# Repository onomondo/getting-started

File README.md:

# Onomondo getting started kit. 

Example forked from [esp-idf repo](https://github.com/espressif/esp-idf/tree/master/examples/protocols/pppos_client). 

## What is this?
The kit is designed to showcase some of the features provided by Onomondo. Already a customer? Head over to [app.onomondo.com/getting-started](https://app.onomondo.com/getting-started) to get a guided tour of the platform and to see the data packets in real-time. 

### Onomondo Connectors 
Specifically, this example is powered by the Onomondo Connectors. It removes complexity (i.e. Cloud SDK) from the device and let the network handle it. Check out the code snippet below - would you have guessed that this is fully encrypted and integrated into the *Azure IoT Hub*? Get more info on Connectors [here](https://help.onomondo.com/what-are-onomondo-connectors). 

```c
//init cellular connectivity
esp_err_t status = initCellular(SIM7xxx, 0);
...
...
// setup of sensor
...
...
// open a socket to a non-existing server
status = openSocket("1.2.3.4", 4321);

// payload formatting
sprintf(payload, "{\"battery\": %f,\"signal\": %f,\"temperature\": %f}", battery, signal, temp);

// transmit payload
status = sendData(payload, strlen(payload), 0);
```

This it what happens on the platform: 
<!--  -->

At this point the data has not yet reached any public networks. Since the SIM has a Connector configured, the payload gets neatly wrapped up and securely handed over to *Azure IoT Hub* (but not limited to *Azure*: Want a webhook event: ✔, any major cloud provider ✔, custom TLS endpoint ✔).    

This is from the *Azure Logs*:

Notice how the network has added a few fields: A timestamp and a sim_id so the device can be identified. In addition to the extra fields everything has been fully encrypted. 

## How to use. 

The kit is fully programmed when you get it. However, you are encouraged to modify the example we have provided. 

First time use: Flick the power switch and the device should come online. The device will search for networks, register on a network and establish a data connection. Touch the touch-pad on the front to transmit a message with the current temperature, battery voltage and last known signal level. After a while the device will enter a low power state. Give it a shake to wake it up again. 

### Get the demo tour
On [app.onomondo.com/getting-started](https://app.onomondo.com/getting-started) you'll get the full tour. 

### Flash a precompiled firmware
In case the stock firmware gets overwritten, you can easily flash the device with a precompiled binary. Download the *ESP flash download tool* [here](https://www.espressif.com/en/support/download/other-tools?keys=download+tool), download the precompiled firmware (**onomondo_getting_started.bin**) from the repo and flash the device. 

These procompiled binaries will in the future include firmware to assist in debugging connectivity with Onomondo. 

### Build and Flash Modified firmware. 

Run `idf.py --ccache -p PORT build flash monitor` to build and flash the project..

(To exit the serial monitor, type ``Ctrl-]``.)

See the [ESP-IDF Getting Started Guide](https://docs.espressif.com/projects/esp-idf/en/latest/get-started/index.html) for full steps to configure and use ESP-IDF to build projects. 

## Troubleshooting
If the device fails to connect (red flashing LED).  
1. Is the sim activated
2. Attaching for the first time can be slow in some cases. 
3. Is the antenna plugged in?
4. Is there sufficient charge on the battery? If the battery is discharged the device won't turn on until it has been plugged into a charger. 

Check the Network logs on the Onomondo platform. Does the platform report any activity?

Plug the device into you computer (use the port marked as MCU Debug on the back). Have a look at the out below and see if anything stands out. Does the modem reponds to any commands? When does it stop responding? 

## Example Output

### SIM7070G Output
```bash
I (451) main: Cpu freq: 160 MhZ
I (451) ACC: Config i2c param
I (461) ACC: Install i2c driver
I (461) ACC: Reading register....
I (481) main: Temperature: 26.500000
I (481) gpio: GPIO[4]| InputEn: 0| OutputEn: 1| OpenDrain: 0| Pullup: 0| Pulldown: 0| Intr:0
I (481) gpio: GPIO[5]| InputEn: 0| OutputEn: 1| OpenDrain: 0| Pullup: 0| Pulldown: 0| Intr:0
I (491) gpio: GPIO[25]| InputEn: 0| OutputEn: 1| OpenDrain: 0| Pullup: 0| Pulldown: 0| Intr:0
I (511) touch_driver: test init: touch pad [6] val is 686
I (511) uart: queue free spaces: 30
I (511) sim800: PWR pin 27
I (511) gpio: GPIO[27]| InputEn: 0| OutputEn: 1| OpenDrain: 0| Pullup: 0| Pulldown: 0| Intr:0
I (521) AT CMD: AT
E (621) esp-modem: esp_modem_dte_send_cmd(352): process command timeout
E (621) dce_service: esp_modem_dce_power_test(251): send command failed
I (721) AT CMD: AT
I (721) AT RESP: AT

E (721) esp-modem: esp_dte_handle_line(136): handle line failed
E (721) esp-modem: AT

I (721) AT RESP: OK

I (721) sim800: Modem is on!
I (731) AT CMD: AT
I (731) AT RESP: AT

E (731) esp-modem: esp_dte_handle_line(136): handle line failed
E (741) esp-modem: AT

I (741) AT RESP: OK

I (751) AT CMD: ATE0
I (751) AT RESP: ATE0

E (751) esp-modem: esp_dte_handle_line(136): handle line failed
E (761) esp-modem: ATE0

I (761) AT RESP: OK

I (761) AT CMD: AT+CGMM
I (771) AT RESP:

I (771) AT RESP: SIMCOM_SIM7070

I (781) AT RESP:

I (781) AT RESP: OK

I (781) AT CMD: AT+CGSN
I (791) AT RESP:

I (791) AT RESP: 861340049970997

I (791) AT RESP:

I (791) AT RESP: OK

I (801) AT CMD: AT+COPS?
I (801) AT RESP:

I (801) AT RESP: +COPS: 1,0,"TDC",7

I (811) AT RESP:

I (811) AT RESP: OK

I (811) AT CMD: AT+CREG?
I (821) AT RESP:

I (821) AT RESP: +CREG: 0,5

I (821) AT RESP:

I (831) AT RESP: OK

I (831) AT CMD: AT+CBANDCFG="CAT-M",3,8,20
I (841) AT RESP:

I (841) AT RESP: OK

I (841) AT CMD: AT+CNMP=38
I (851) AT RESP:

I (851) AT RESP: OK

I (851) esp-modem: No handler for line: OK

E (851) esp-modem: OK

E (1341) esp-modem: esp_modem_dte_send_cmd(352): process command timeout
I (1341) sim800: Modem INIT OK, 0x3ffbf604
I (1341) AT CMD: AT+IFC=0,0
I (1341) AT RESP:

I (1341) AT RESP: OK

I (1351) AT CMD: AT+CREG?
I (1351) AT RESP:

I (1351) AT RESP: +CREG: 0,5

I (1361) AT RESP:

I (1361) AT RESP: OK

I (1361) cellular: Module: SIMCOM_SIM7070
I (1371) cellular: Operator: "TDC"
I (1371) cellular: IMEI: 861340049970997
I (1381) cellular: IMSI:
I (1381) AT CMD: AT+CSQ
I (1381) AT RESP:

I (1391) AT RESP: +CSQ: 31,99

I (1391) AT RESP:

I (1391) AT RESP: OK

I (1401) cellular: rssi: 31, ber: 99
I (1401) AT CMD: AT+CEDRXS=1,4,"0010"
I (1411) AT RESP:

I (1411) AT RESP: OK

I (1411) AT CMD: AT+CEDRXRDP
I (1421) AT RESP:

I (1421) AT RESP: +CEDRXRDP: 4,"0010","0010","0000"

I (1421) eDRX CHECK: Supported
I (1431) AT RESP:

I (1431) AT RESP: OK

I (1431) AT CMD: AT+CPSMRDP
I (1441) AT RESP:

I (1441) AT RESP: +CPSMRDP: 0,20,14400,0,0,3600

I (1441) PSM CHECK: +CPSMRDP: 0,20,14400,0,0,3600

I (1451) PSM CHECK: 0,20,14400,0,0,3600
I (1451) PSM CHECK: Active: 0
I (1461) AT RESP:

I (1461) AT RESP: OK

I (1461) AT CMD: AT+CPSI?
I (1471) AT RESP:

I (1481) AT RESP: +CPSI: LTE CAT-M1,Online,238-01,0x07D0,12024586,465,EUTRAN-BAND20,6350,5,5,-16,-83,-53,10

E (1481) esp-modem: esp_dte_handle_line(136): handle line failed
E (1491) esp-modem: +CPSI: LTE CAT-M1,Online,238-01,0x07D0,12024586,465,EUTRAN-BAND20,6350,5,5,-16,-83,-53,10

I (1501) AT RESP:

I (1501) AT RESP: OK

I (1501) AT CMD: AT+CPSMRDP
I (1511) AT RESP:

I (1511) AT RESP: +CPSMRDP: 0,20,14400,0,0,3600

I (1521) PSM CHECK: +CPSMRDP: 0,20,14400,0,0,3600

I (1521) PSM CHECK: 0,20,14400,0,0,3600
I (1531) PSM CHECK: Active: 0
I (1531) AT RESP:

I (1531) AT RESP: OK

I (1541) AT CMD: AT+CGDCONT=1,"IP","onomondo"
I (1551) AT RESP:

I (1551) AT RESP: OK

I (1551) dce_service: define pdp context ok
I (1551) sim800: Working mode is changed! :D
I (1561) AT CMD: ATD*99#
I (1561) AT RESP:

I (1561) AT RESP: CONNECT 150000000

I (1671) cellular: Modem PPP Started
I (1671) cellular: PPP state changed event 259
I (1671) cellular: PPP state changed event 262
I (1691) cellular: PPP state changed event 263
I (1691) cellular: PPP state changed event 265
I (1711) esp-netif_lwip-ppp: Connected
I (1711) esp-netif_lwip-ppp: Name Server1: 10.85.59.251
I (1711) esp-netif_lwip-ppp: Name Server2: 10.85.59.242
I (1721) cellular: Modem Connect to PPP Server
I (1721) cellular: ~~~~~~~~~~~~~~
I (1731) cellular: IP          : 100.68.57.55
I (1731) cellular: Netmask     : 255.255.255.255
I (1741) cellular: Gateway     : 10.64.64.64
I (1741) cellular: Name Server1: 10.85.59.251
I (1751) cellular: Name Server2: 10.85.59.242
I (1751) cellular: ~~~~~~~~~~~~~~
I (1761) cellular: GOT ip event!!!
I (1761) cellular: PPP state changed event 266
I (1771) cellular: Socket created, connecting to 1.2.3.4:4321
I (3161) Transmit: {"battery": 0.284000,"signal": 31.000000,"temperature": 26.625000}
W (20361) ACC: Wakeup interrupt NOT active...,00000000
```

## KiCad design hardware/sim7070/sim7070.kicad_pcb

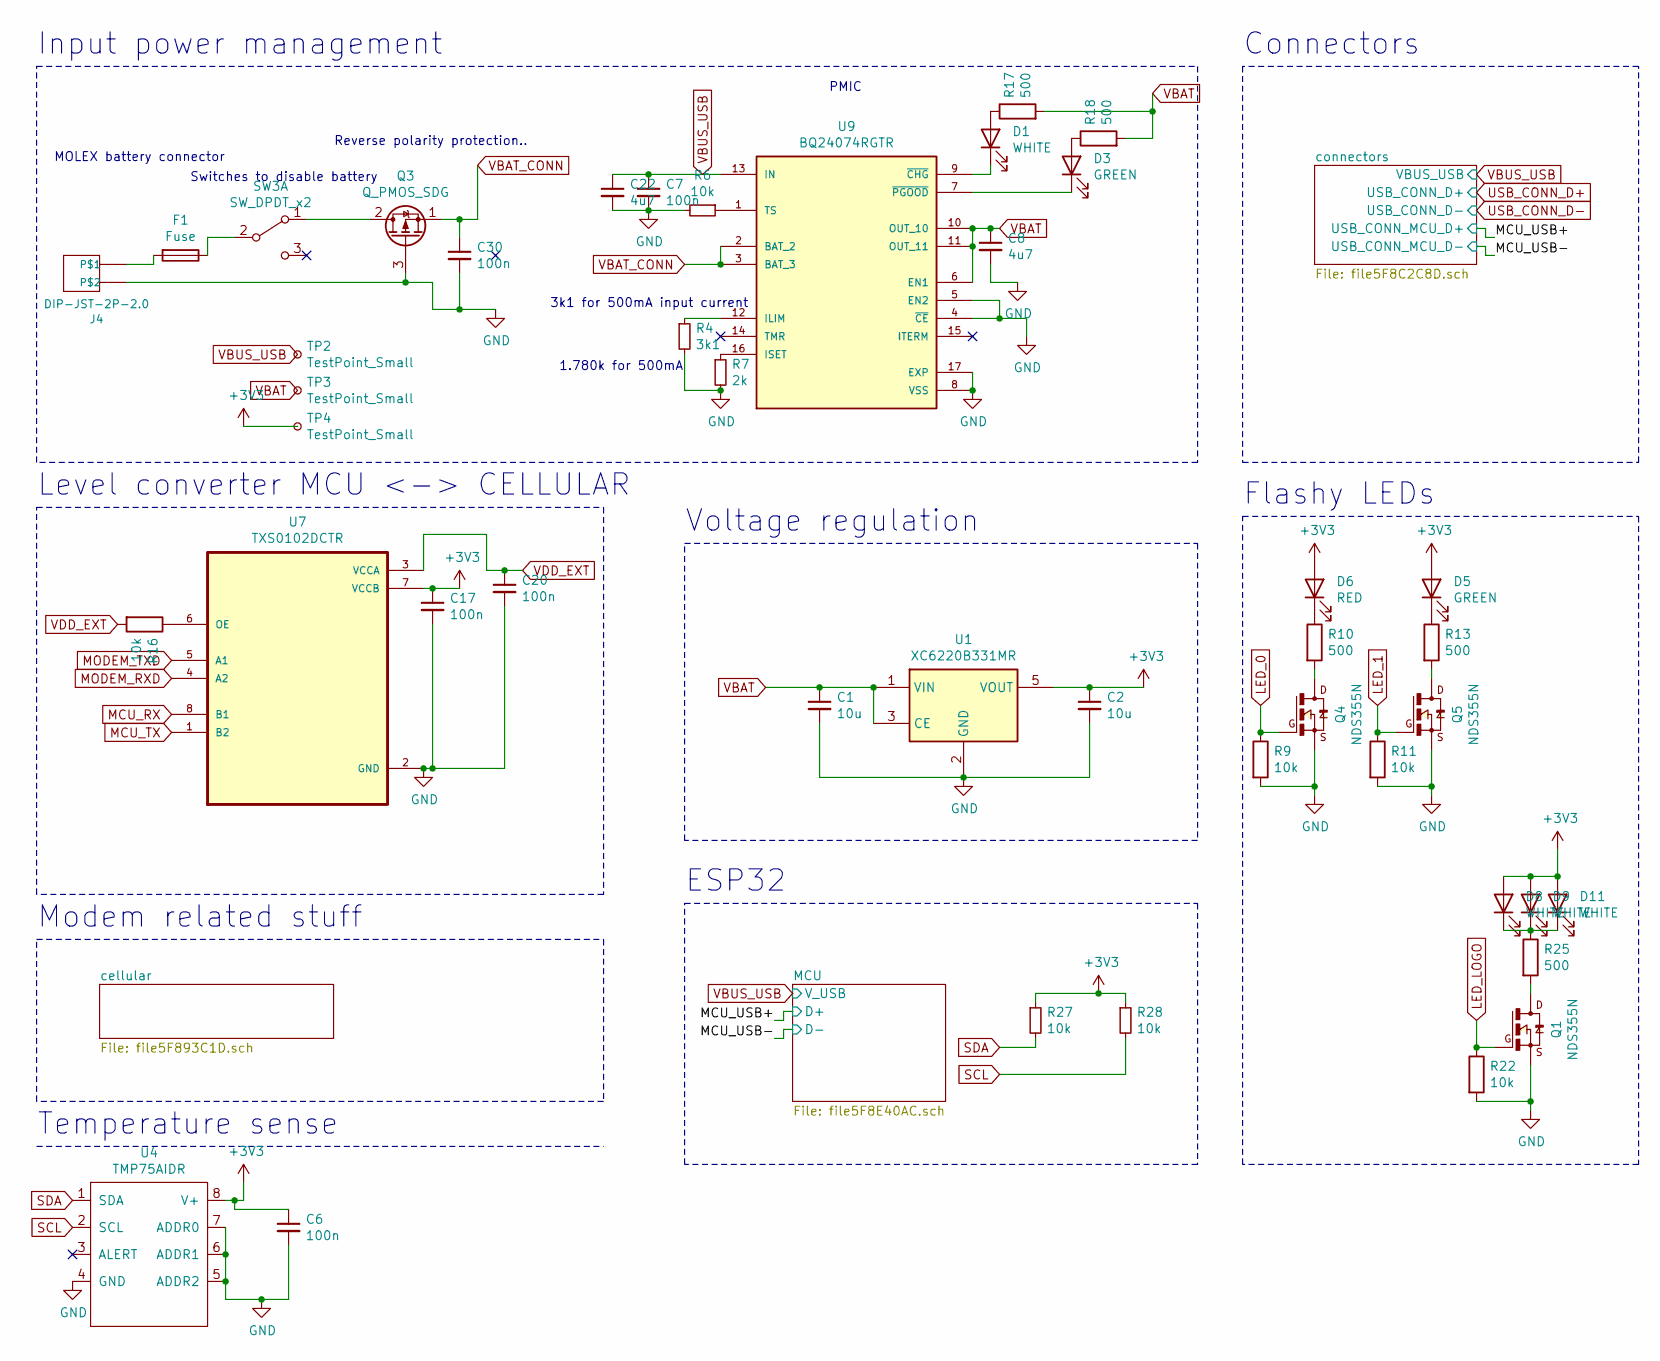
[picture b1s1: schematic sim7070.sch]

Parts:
C1, C2: 10u; C_0603_1608Metric; LCSC C19702
C6, C7, C17, C20, C30: 100n; C_0402_1005Metric; LCSC C1525
C8: 4u7; C_1206_3216Metric; LCSC C29823
C22: 4u7; C_1206_3216Metric
D1, D8, D9, D11: WHITE; LED_0603_1608Metric; LCSC C2290
D3: GREEN; LED_0603_1608Metric
D5: GREEN; LED_0603_1608Metric; LCSC C2286
D6: RED; LED_0603_1608Metric; LCSC C2286
F1: Fuse; Fuse_0603_1608Metric; LCSC C163117
J4: DIP-JST-2P-2.0; JST_PH_S2B-PH-K_1x02_P2.00mm_Horizontal; LCSC C173752
Q1, Q4, Q5: NDS355N; SSOT-3; LCSC C113202
Q3: Q_PMOS_SDG; SOT-23-MOSFET; LCSC C10487
R4: 3k1; R_0402_1005Metric; LCSC C26077
R6, R9, R11, R22, R27, R28: 10k; R_0402_1005Metric; LCSC C25531
R7: 2k; R_0402_1005Metric; LCSC C25552
R10, R13, R17, R18, R25: 500; R_0603_1608Metric; LCSC C23179
R16: 10k; R_0402_1005Metric
SW3: SW_DPDT_x2; SWITCH_3A; LCSC C319015
TP2, TP3, TP4: TestPoint_Small; TestPoint_Pad_1.5x1.5mm
U1: XC6220B331MR; SOT-23-5; LCSC C86534
U4: TMP75AIDR; SOIC-8_3.9x4.9mm_P1.27mm; LCSC C30389
U7: TXS0102DCTR; SOP65P400X130-8N; LCSC C324082
U9: BQ24074RGTR; QFN50P300X300X100-17N; PARTREV M; LCSC C54313

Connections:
+3V3: C2.1, C6.1, C17.1, D5.2 (A), D6.2 (A), D8.2 (A), D9.2 (A), D11.2 (A), R27.1, R28.1, TP4.1, U1.5 (VOUT), U4.8 (V+), U7.7 (VCCB); also elsewhere on the board
GND: C1.2, C2.2, C6.2, C7.2, C8.2, C17.2, C20.2, C22.2, C30.2, J4.2, Q1.2, Q3.3 (G), Q4.2, Q5.2, R4.2, R6.2, R7.2, R9.2, R11.2, R22.2, U1.2 (GND), U4.4 (GND), U4.5 (ADDR2), U4.6 (ADDR1), U4.7 (ADDR0), U7.2 (GND), U9.4 (~CE), U9.5 (EN2), U9.8 (VSS), U9.17 (EXP), U9.18, U9.19, U9.20, U9.21, U9.22; also elsewhere on the board
LED_0: Q4.1, R9.1; also elsewhere on the board
LED_1: Q5.1, R11.1; also elsewhere on the board
LED_LOGO: Q1.1, R22.1; also elsewhere on the board
MCU_RX: U7.8 (B1); also elsewhere on the board
MCU_TX: U7.1 (B2); also elsewhere on the board
MODEM_RXD: U7.4 (A2); also elsewhere on the board
MODEM_TXD: U7.5 (A1); also elsewhere on the board
unnamed: D1.1 (K), U9.9 (~CHG)
unnamed: D1.2 (A), R17.1
unnamed: D3.1 (K), U9.7 (~PGOOD)
unnamed: D3.2 (A), R18.1
unnamed: D5.1 (K), R13.1
unnamed: D6.1 (K), R10.1
unnamed: D8.1 (K), D9.1 (K), D11.1 (K), R25.1
unnamed: F1.1, SW3.2 (B)
unnamed: F1.2, J4.1
unnamed: Q1.3, R25.2
unnamed: Q3.2 (D), SW3.1 (A)
unnamed: Q4.3, R10.2
unnamed: Q5.3, R13.2
unnamed: R4.1, U9.12 (ILIM)
unnamed: R6.1, U9.1 (TS)
unnamed: R7.1, U9.16 (ISET)
unnamed: R16.1, U7.6 (OE)
SCL: R28.2, U4.2 (SCL); also elsewhere on the board
SDA: R27.2, U4.1 (SDA); also elsewhere on the board
VBAT: C1.1, C8.1, R17.2, R18.2, TP3.1, U1.1 (VIN), U1.3 (CE), U9.6 (EN1), U9.10 (OUT_10), U9.11 (OUT_11); also elsewhere on the board
VBAT_CONN: C30.1, Q3.1 (S), U9.2 (BAT_2), U9.3 (BAT_3); also elsewhere on the board
VBUS_USB: C7.1, C22.1, TP2.1, U9.13 (IN); also elsewhere on the board
VDD_EXT: C20.1, R16.2, U7.3 (VCCA); also elsewhere on the board

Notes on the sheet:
Reverse polarity protection..
Switches to disable battery
MOLEX battery connector
1.780k for 500mA
3k1 for 500mA input current
PMIC
Input power management
Level converter MCU <-> CELLULAR
Voltage regulation
Modem related stuff
ESP32
Connectors
Flashy LEDs
Temperature sense

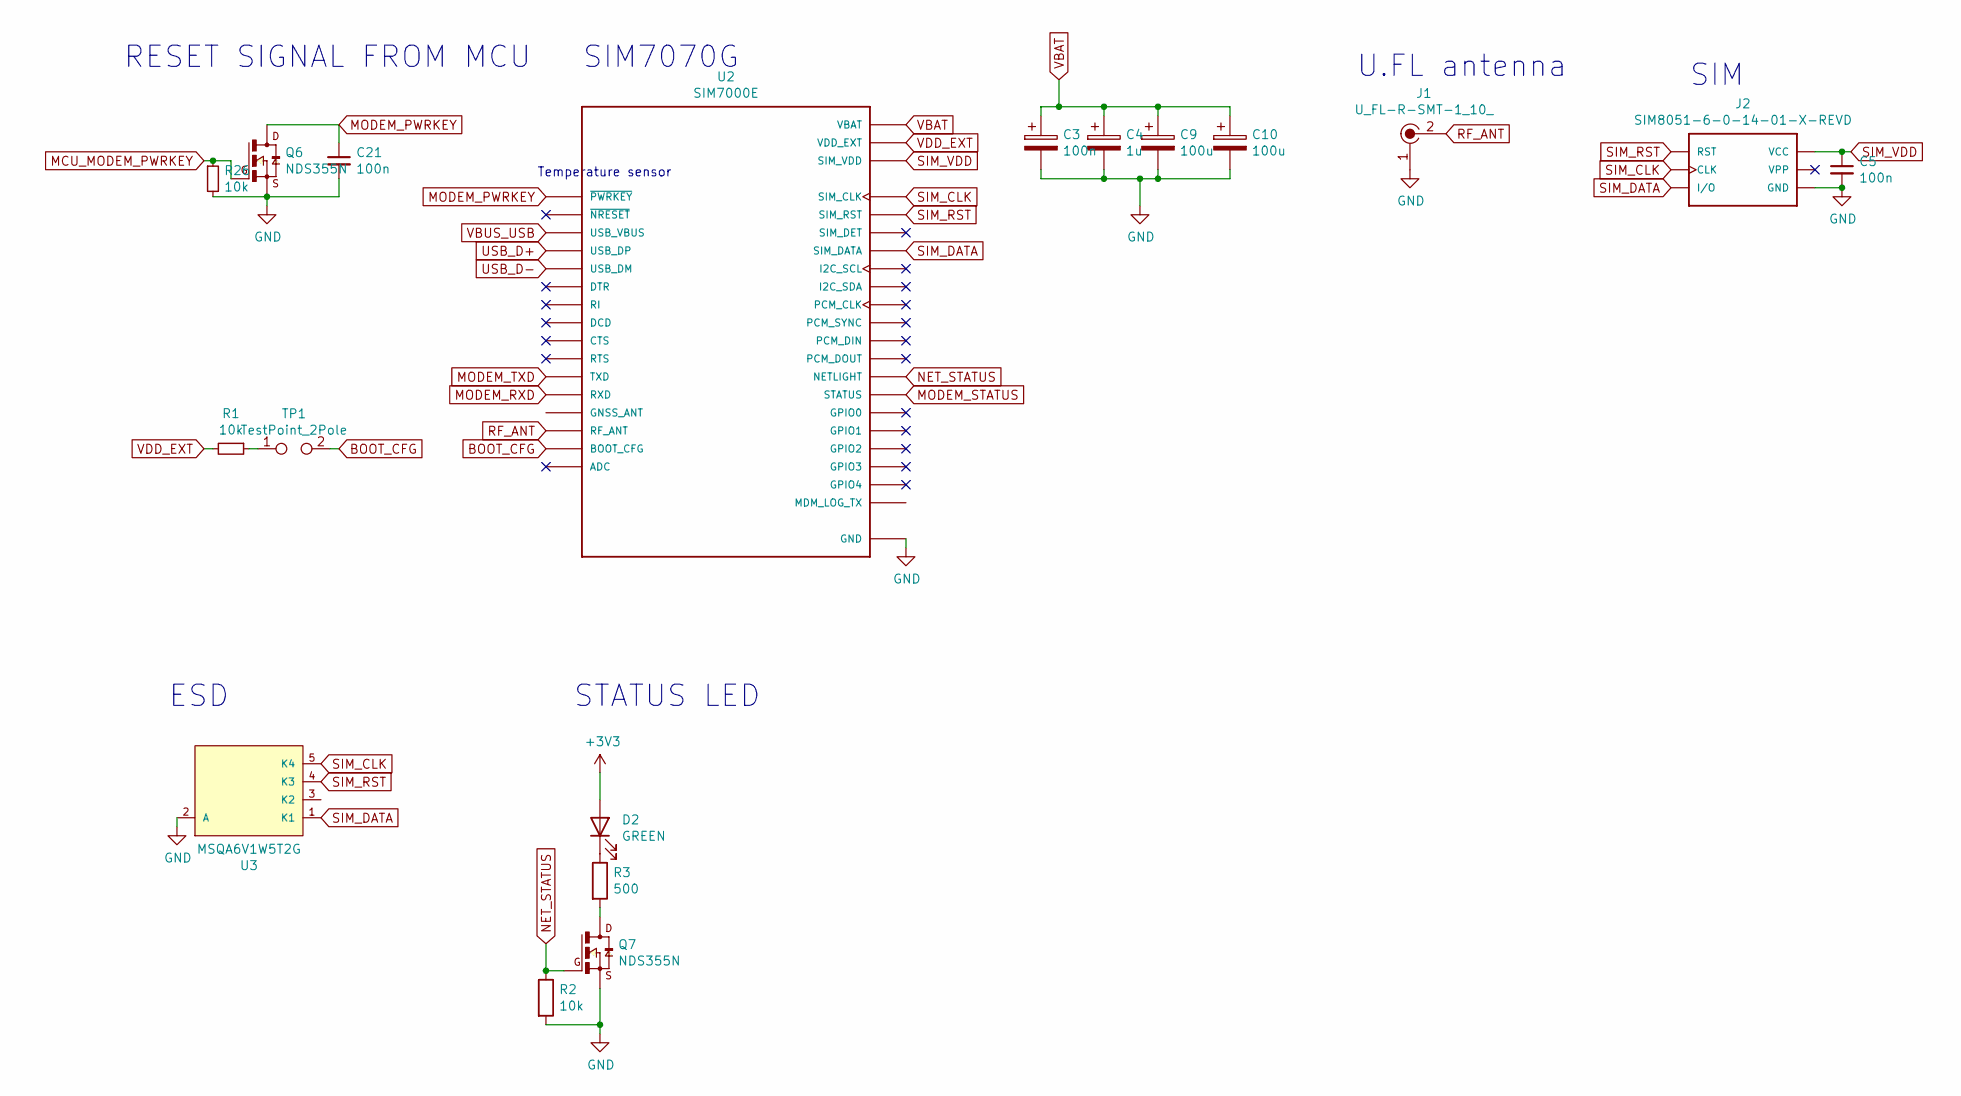
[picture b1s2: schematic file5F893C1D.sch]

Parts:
C3, C5, C21: 100n; C_0402_1005Metric; LCSC C1525
C4: 1u; C_0805_2012Metric; LCSC C28323
C9: 100u; C_1206_3216Metric; LCSC C15008
C10: 100u; C_1206_3216Metric
D2: GREEN; LED_0603_1608Metric
J1: U_FL-R-SMT-1_10_; Coax_Conn_U.FL; MPN U.FL-R-SMT-1(10); Digi-Key_PN H11891CT-ND
J2: SIM8051-6-0-14-01-X-REVD; SNO-1305-B_NANO_SIM; LCSC C111371
Q6, Q7: NDS355N; SSOT-3; LCSC C113202
R1: 10k; R_0402_1005Metric
R2, R26: 10k; R_0402_1005Metric; LCSC C25531
R3: 500; R_0603_1608Metric; LCSC C23179
TP1: TestPoint_2Pole; SolderJumper-2_P1.3mm_Open_Pad1.0x1.5mm
U2: SIM7000E; SIMCON_SIM7000E
U3: MSQA6V1W5T2G; On_Semiconductor-MSQA6V1W5T2G-Manufacturer_Recommended; LCSC C232563

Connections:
+3V3: D2.2 (A); also elsewhere on the board
BOOT_CFG: TP1.2, U2.6 (BOOT_CFG)
GND: C3.2, C4.2, C5.2, C9.2, C10.2, C21.2, J1.1, J2.C5 (GND), Q6.2, Q7.2, R2.2, R26.2, U2.2 (GND), U2.17 (GND), U2.18 (GND), U2.29 (GND), U2.39 (GND), U2.45 (GND), U2.46 (GND), U2.54 (GND), U2.58 (GND), U2.59 (GND), U2.61 (GND), U2.62 (GND), U2.63 (GND), U2.64 (GND), U2.65 (GND), U3.2 (A); also elsewhere on the board
MCU_MODEM_PWRKEY: Q6.1, R26.1; also elsewhere on the board
MODEM_PWRKEY: C21.1, Q6.3, U2.1 (~PWRKEY~); also elsewhere on the board
MODEM_RXD: U2.10 (RXD); also elsewhere on the board
MODEM_STATUS: U2.66 (STATUS)
MODEM_TXD: U2.9 (TXD); also elsewhere on the board
NET_STATUS: Q7.1, R2.1, U2.52 (NETLIGHT)
unnamed: D2.1 (K), R3.1
unnamed: Q7.3, R3.2
unnamed: R1.1, TP1.1
RF_ANT: J1.2, U2.60 (RF_ANT)
SIM_CLK: J2.C3 (CLK), U2.32 (SIM_CLK), U3.5 (K4)
SIM_DATA: J2.C7 (I/O), U2.31 (SIM_DATA), U3.1 (K1)
SIM_RST: J2.C2 (RST), U2.33 (SIM_RST), U3.4 (K3)
SIM_VDD: C5.1, J2.C1 (VCC), U2.30 (SIM_VDD)
USB_CONN_D+: U2.27 (USB_DP); also elsewhere on the board
USB_CONN_D-: U2.28 (USB_DM); also elsewhere on the board
VBAT: C3.1, C4.1, C9.1, C10.1, U2.55 (VBAT), U2.56 (VBAT), U2.57 (VBAT); also elsewhere on the board
VBUS_USB: U2.24 (USB_VBUS); also elsewhere on the board
VDD_EXT: R1.2, U2.15 (VDD_EXT); also elsewhere on the board

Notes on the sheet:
Temperature sensor
SIM7070G
U.FL antenna
SIM
RESET SIGNAL FROM MCU
ESD
STATUS LED

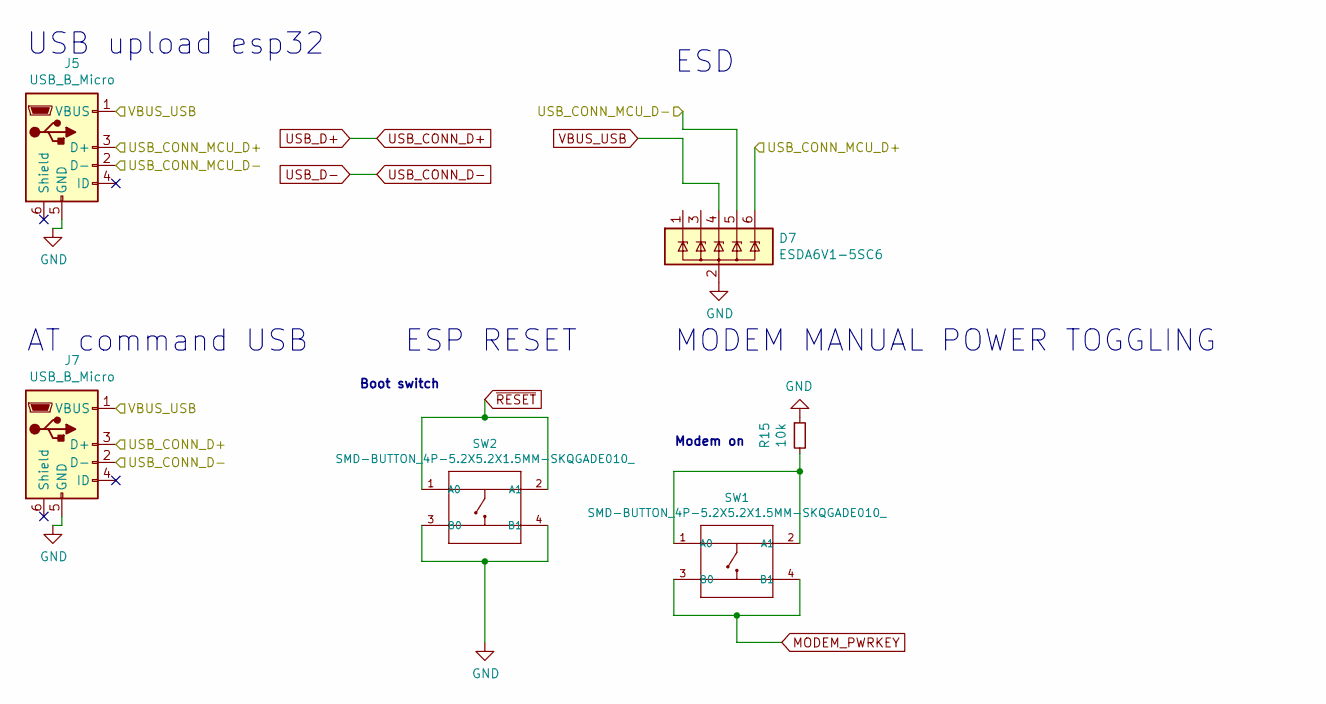
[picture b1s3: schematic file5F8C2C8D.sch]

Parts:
D7: ESDA6V1-5SC6; SOT-23-6; LCSC C6650
J5, J7: USB_B_Micro; USB_Micro_B_JLC; LCSC C404969
R15: 10k; R_0402_1005Metric; LCSC C25531
SW1, SW2: SMD-BUTTON_4P-5.2X5.2X1.5MM-SKQGADE010_; SW4-SMD-5.2X5.2X1.5MM; MPN SKQGADE010; LCSC C318887

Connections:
/MCU_USB+: D7.6 (IO5), J5.3 (D+); also elsewhere on the board
/MCU_USB-: D7.5 (IO4), J5.2 (D-); also elsewhere on the board
GND: D7.2 (GND), J5.5 (GND), J7.5 (GND), R15.1, SW2.3 (B0), SW2.4 (B1); also elsewhere on the board
MODEM_PWRKEY: SW1.3 (B0), SW1.4 (B1); also elsewhere on the board
unnamed: R15.2, SW1.1 (A0), SW1.2 (A1)
USB_CONN_D+: J7.3 (D+); also elsewhere on the board
USB_CONN_D-: J7.2 (D-); also elsewhere on the board
VBUS_USB: D7.4 (IO3), J5.1 (VBUS), J7.1 (VBUS); also elsewhere on the board
~RESET~: SW2.1 (A0), SW2.2 (A1); also elsewhere on the board

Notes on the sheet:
Boot switch
Modem on
USB upload esp32
AT command USB
ESD
ESP RESET
MODEM MANUAL POWER TOGGLING

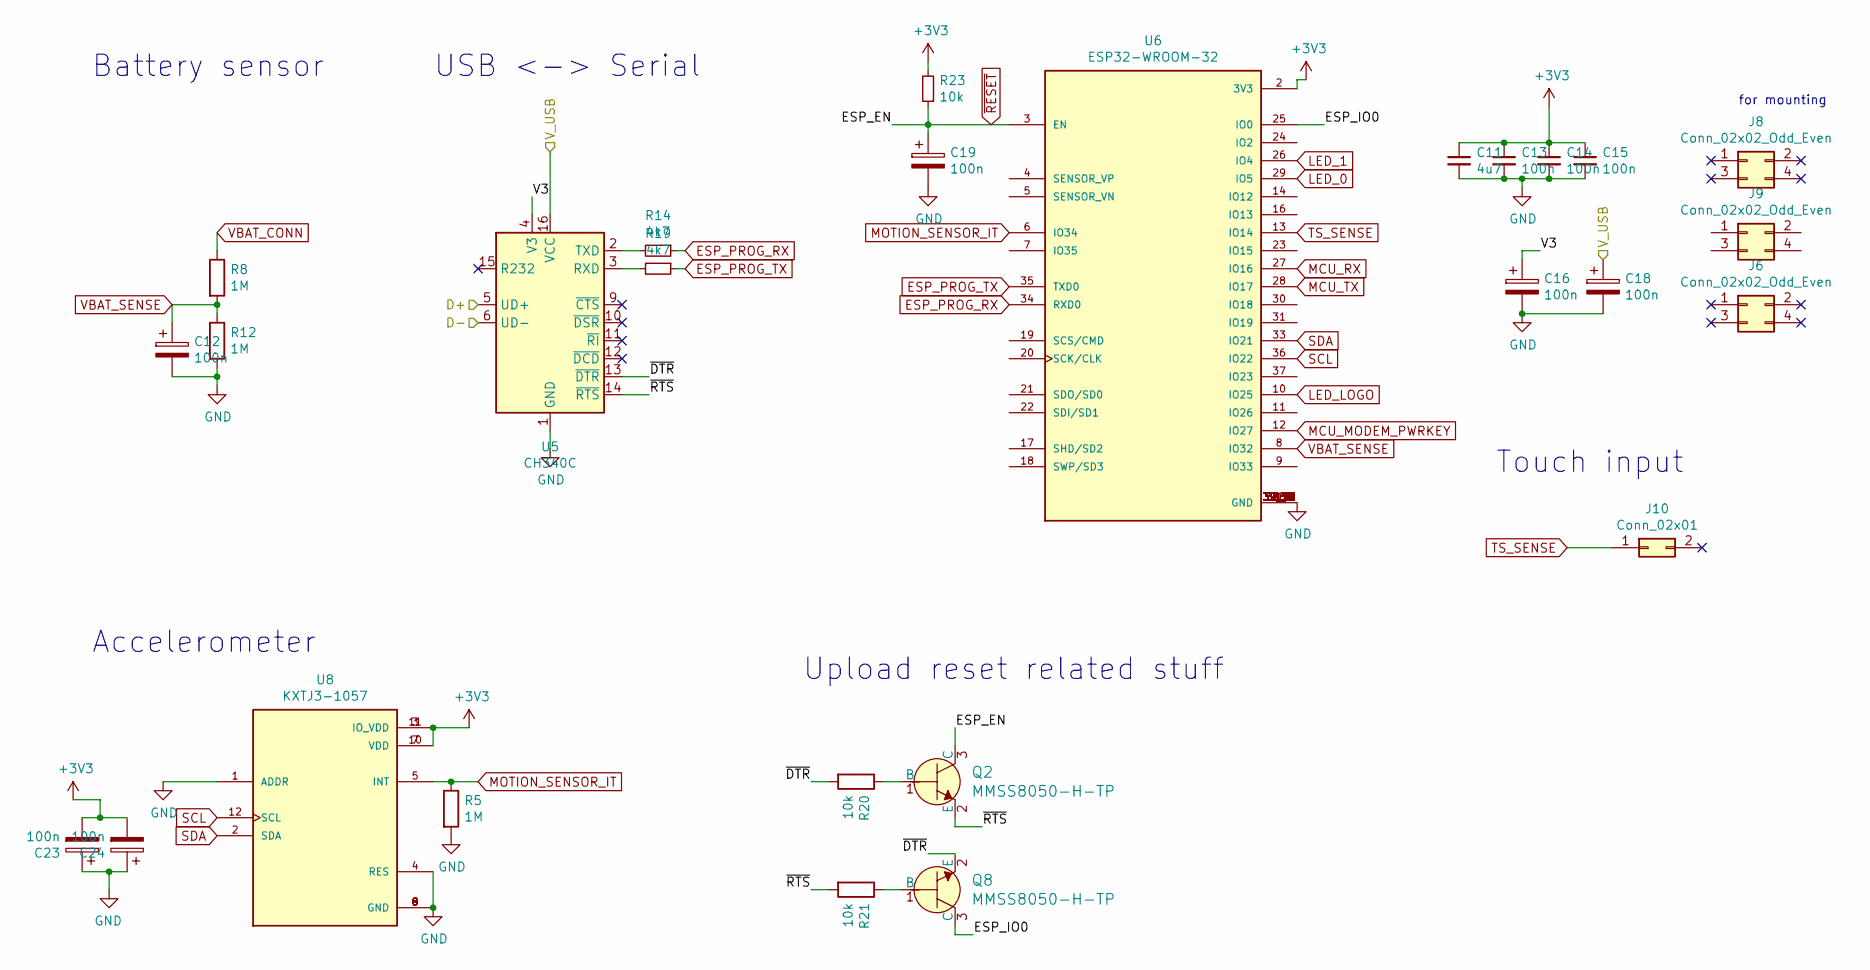
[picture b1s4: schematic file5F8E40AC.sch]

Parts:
C11: 4u7; C_1206_3216Metric
C12, C13, C14, C15, C16, C18, C19, C23, C24: 100n; C_0402_1005Metric; LCSC C1525
J6, J8, J9: Conn_02x02_Odd_Even; PinSocket_2x02_P2.54mm_Vertical_centered; LCSC C239342
J10: Conn_02x01; PinSocket_1x02_P2.54mm_Vertical; LCSC C124411
Q2, Q8: MMSS8050-H-TP; SOT-23-3; MPN MMSS8050-H-TP; Digi-Key_PN MMSS8050-H-TPMSCT-ND
R5, R8, R12: 1M; R_0402_1005Metric; LCSC C26087
R14, R19: 4k7; R_0402_1005Metric; LCSC C25900
R20, R21, R23: 10k; R_0402_1005Metric; LCSC C25531
U5: CH340C; SOIC-16_3.9x9.9mm_P1.27mm; LCSC C84681
U6: ESP32-WROOM-32; MODULE_ESP32-WROOM-32; PARTREV 2.9; LCSC C82899
U8: KXTJ3-1057; KIONIX_KXTJ3-1057; PARTREV 4.0; LCSC C442603

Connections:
+3V3: C11.1, C13.1, C14.1, C15.1, C23.2, C24.2, R23.2, U6.2 (3V3), U8.3 (IO_VDD), U8.7 (VDD), U8.10 (VDD), U8.11 (IO_VDD); also elsewhere on the board
/MCU/ESP_IO0: Q8.3 (C), U6.25 (IO0)
/MCU/V3: C16.1, U5.4 (V3)
/MCU/~DTR~: Q8.2 (E), R20.2, U5.13 (~DTR)
/MCU/~RTS~: Q2.2 (E), R21.2, U5.14 (~RTS)
/MCU_USB+: U5.5 (UD+); also elsewhere on the board
/MCU_USB-: U5.6 (UD-); also elsewhere on the board
ESP_PROG_RX: R14.1, U6.34 (RXD0)
ESP_PROG_TX: R19.1, U6.35 (TXD0)
GND: C11.2, C12.2, C13.2, C14.2, C15.2, C16.2, C18.2, C19.2, C23.1, C24.1, R5.2, R12.2, U5.1 (GND), U6.1 (GND), U6.15 (GND), U6.38 (GND), U6.39_1 (GND), U6.39_2 (GND), U6.39_3 (GND), U6.39_4 (GND), U6.39_5 (GND), U6.39_6 (GND), U6.39_7 (GND), U6.39_8 (GND), U6.39_9 (GND), U6.39_10 (GND), U6.39_11 (GND), U6.39_12 (GND), U6.39_13 (GND), U6.39_14 (GND), U6.39_15 (GND), U6.39_16 (GND), U6.39_17 (GND), U6.39_18 (GND), U6.39_19 (GND), U6.39_20 (GND), U6.39_21 (GND), U8.1 (ADDR), U8.4 (RES), U8.6 (GND), U8.8 (GND), U8.9 (GND); also elsewhere on the board
LED_0: U6.29 (IO5); also elsewhere on the board
LED_1: U6.26 (IO4); also elsewhere on the board
LED_LOGO: U6.10 (IO25); also elsewhere on the board
MCU_MODEM_PWRKEY: U6.12 (IO27); also elsewhere on the board
MCU_RX: U6.27 (IO16); also elsewhere on the board
MCU_TX: U6.28 (IO17); also elsewhere on the board
MOTION_SENSOR_IT: R5.1, U6.6 (IO34), U8.5 (INT)
unnamed: Q2.1 (B), R20.1
unnamed: Q8.1 (B), R21.1
unnamed: R14.2, U5.2 (TXD)
unnamed: R19.2, U5.3 (RXD)
SCL: U6.36 (IO22), U8.12 (SCL); also elsewhere on the board
SDA: U6.33 (IO21), U8.2 (SDA); also elsewhere on the board
TS_SENSE: J10.1, U6.13 (IO14)
VBAT_CONN: R8.1; also elsewhere on the board
VBAT_SENSE: C12.1, R8.2, R12.1, U6.8 (IO32)
VBUS_USB: C18.1, U5.16 (VCC); also elsewhere on the board
~RESET~: C19.1, Q2.3 (C), R23.1, U6.3 (EN); also elsewhere on the board

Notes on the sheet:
for mounting
USB <-> Serial
Battery sensor
Accelerometer
Touch input
Upload reset related stuff

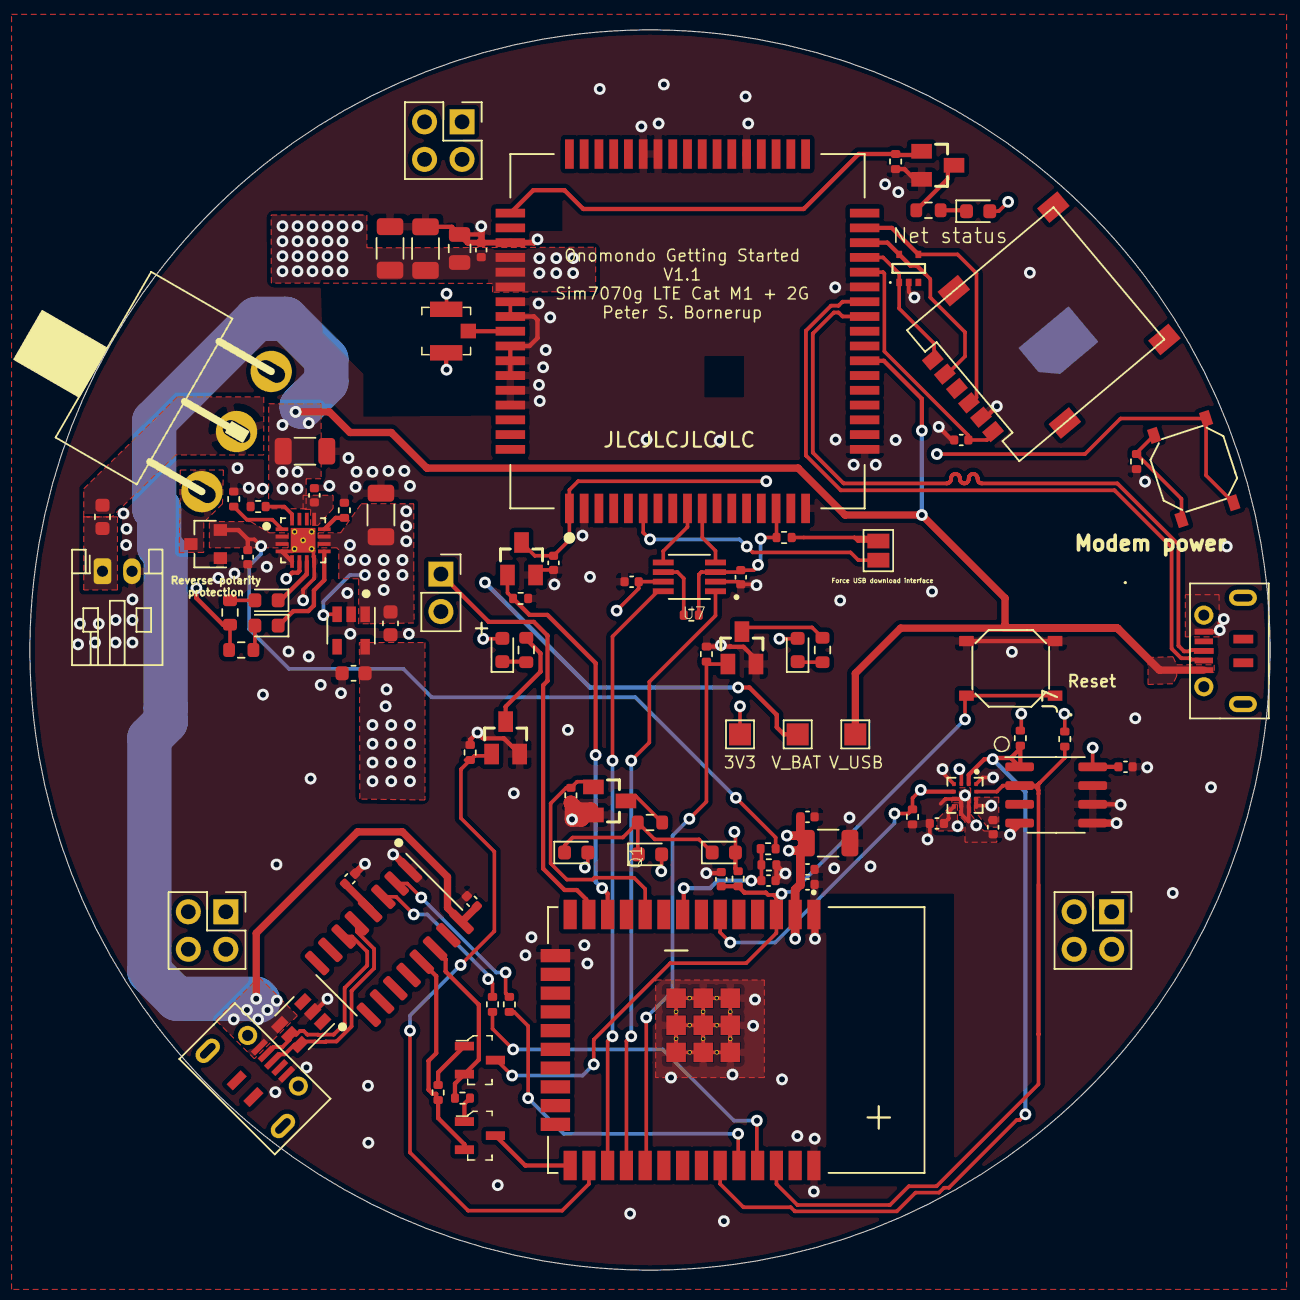
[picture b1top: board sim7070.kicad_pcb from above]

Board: 4 copper layers, 84.0 x 84.0 mm, 95 parts (0 on the bottom side), 63 nets.

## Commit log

2021-06-02 Added .ignore
2021-06-02 Basic funtionality. OTA comming later. Very much untested.... :)
2021-06-29 Sensor libs
2021-07-23 udp, tested and working
2021-07-23 changed default apn. UDP not supported for the conenctor. Changed back to TCP
2021-08-10 Fixed the last stuff before publishing.
2021-08-10 Formatting
2021-08-11 Edits to README
2021-08-19 added img of device
2021-08-23 added design files for the curious reader
2021-08-24 clears the fplmn list on bad attach. Works great with deactivated sims etc. Furthermore, give device time to automatically attach upon boot. In many cases this will happen before anything else. Expli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
2021-08-25 Added support for netscan. Fixed FIFO overflow in edge-cases
2021-08-25 additional check for home network
2021-08-30 added watchdog timeout. Hopefully never needed, but a last resort failsafe
2021-09-03 added precompiled firmware
2021-09-14 small connectin changes.. Set APN ealier to avoid issues when sim is changed to a different profile
2021-09-23 Bit more explicit handling on power down
2021-09-23 Different handling of PSM set param
2021-09-23 pam param
2021-09-24 watchdog pings
2021-09-24 disable eDRX in watchdog mode
2021-09-24 http request w. random addresss
2021-09-27 Watchdog w. random DNS lookup + 2kB http data post
2021-09-29 calloc instead to make use no escape characters does weird stuff
2021-09-29 adjusted the automatic threshold of the touch pad.
2021-10-01 light turns on now. Do that for production ready devices
2021-11-09 Enable more bands default
2021-11-16 try longer to use previous network. Issues with LTE and telia caused the device to not attach...
2021-12-07 added port 6000 for HTTP request so each device will have same code for future use. Maybe remove explicit attach to network..
2022-01-06 Mostly stable. Missing data. DNS is repeated for some reason...?
2022-01-13 Stable for now. LIBat in the future..
2022-01-17 Device stays on longer to be able to respond to pings...
2022-01-19 General clean up
2022-01-24 linting
2022-01-25 mainly linting
2022-03-01 update to rev2
2022-03-15 update to ver 4.4 of esp-idf
2022-04-19 detect when modem locks up. add support for hard-reset
2022-04-27 update to new structure
2022-05-05 all ICCID to all http(s) querys
2022-05-18 statemashine haxxs peter style
2022-05-27 i forgot what
2022-05-27 Add detection of failed modem. Add option to issue hard reset. Add proper config for APN
2022-06-01 minor cleanup
2022-06-07 add support to select tech. from menuconfig.
